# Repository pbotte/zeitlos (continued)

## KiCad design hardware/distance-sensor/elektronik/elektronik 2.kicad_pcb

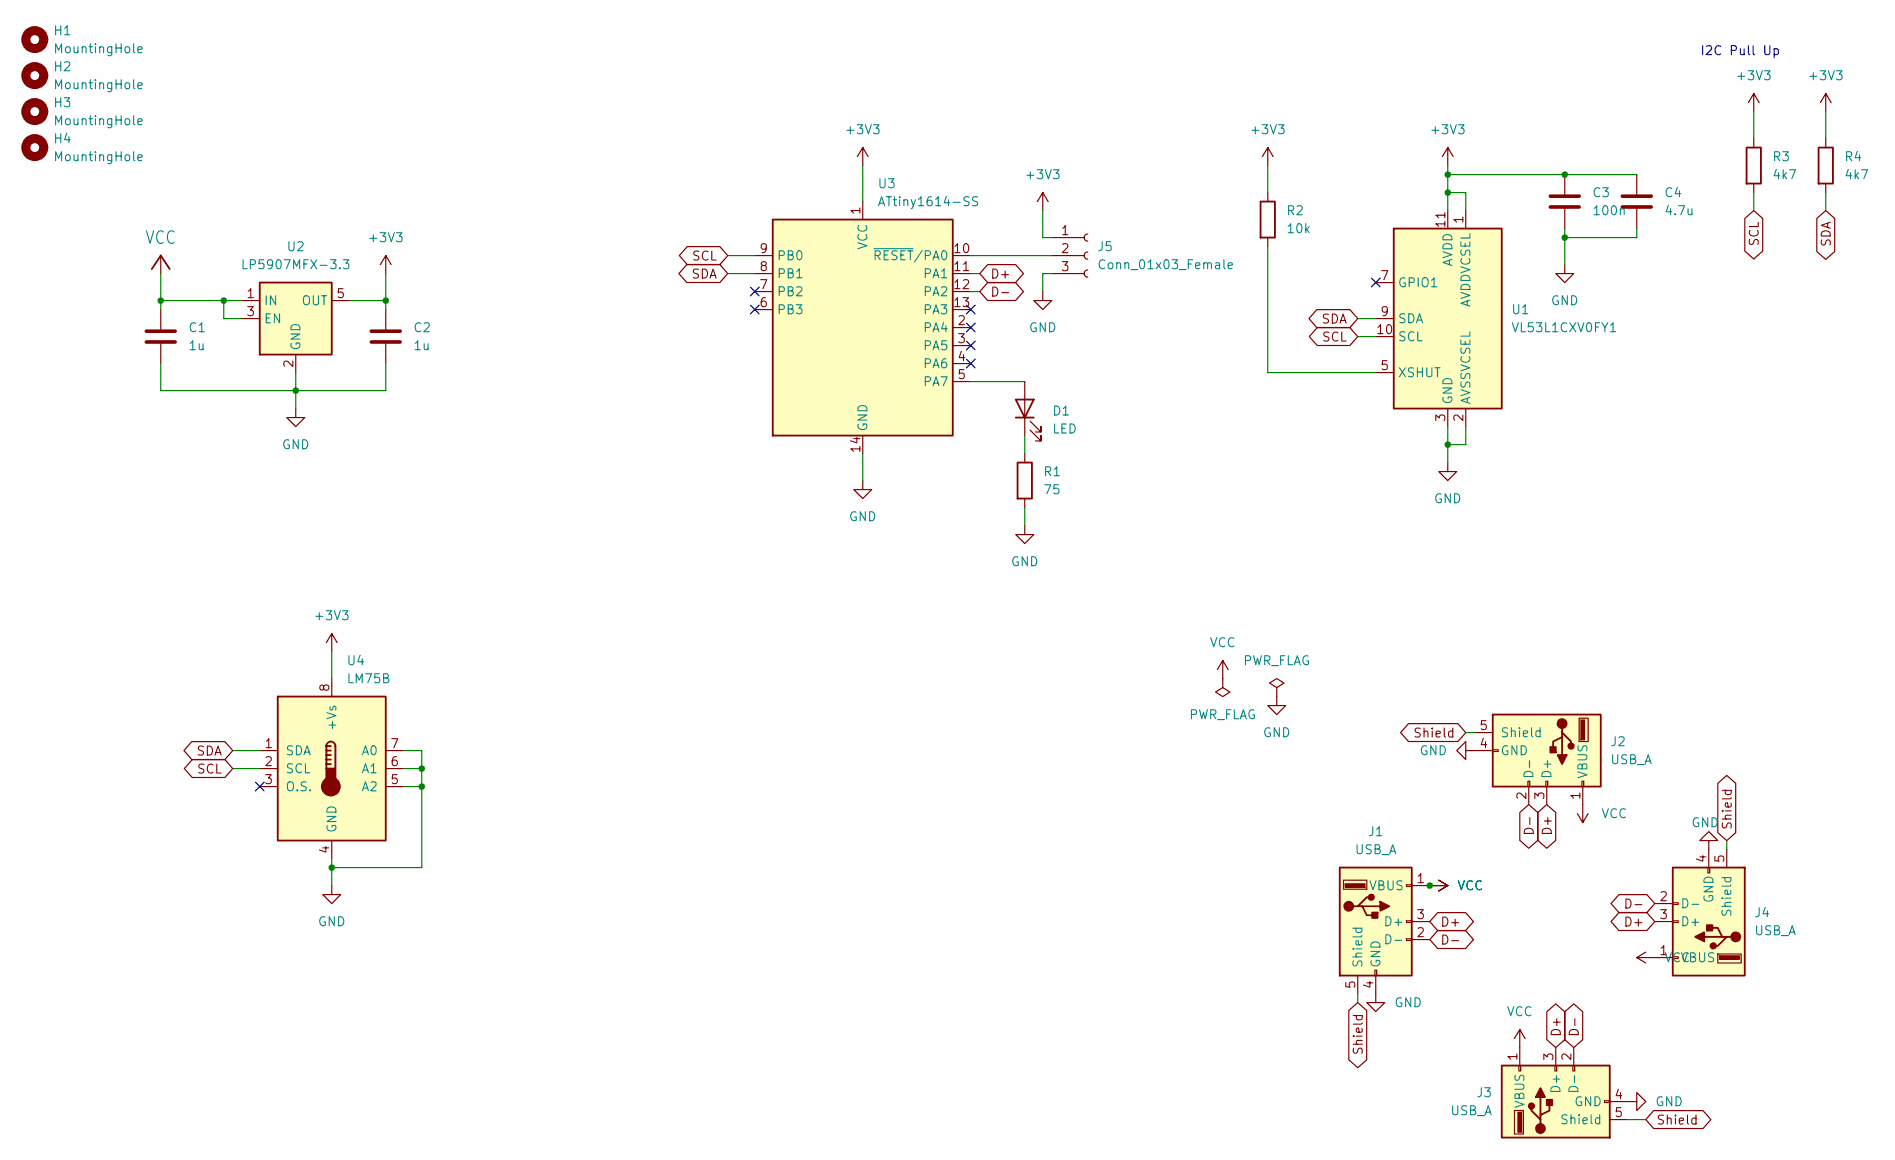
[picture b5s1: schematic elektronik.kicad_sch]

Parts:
C1, C2: 1u; C_1206_3216Metric
C3: 100n; R_1206_3216Metric
C4: 4.7u; R_1206_3216Metric
D1: LED; LED_1206_3216Metric
H1, H2, H3, H4: MountingHole; MountingHole_3.2mm_M3
J1, J2, J3, J4: USB_A; Conn_USB_A_Jack
J5: Conn_01x03_Female; PinSocket_1x03_P2.54mm_Vertical
R1: 75; R_1206_3216Metric
R2: 10k; R_1206_3216Metric
R3, R4: 4k7; R_1206_3216Metric
U1: VL53L1CXV0FY1; ST_VL53L1x
U2: LP5907MFX-3.3; SOT-23-5
U3: ATtiny1614-SS; SOIC-14_3.9x8.7mm_P1.27mm
U4: LM75B; VSSOP-8_3.0x3.0mm_P0.65mm

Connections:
+3V3: C2.1, C3.1, C4.1, J5.1, R2.1, R3.1, R4.1, U1.1 (AVDDVCSEL), U1.11 (AVDD), U2.5 (OUT), U3.1 (VCC), U4.8 (+Vs)
D+: J1.3 (D+), J2.3 (D+), J3.3 (D+), J4.3 (D+), U3.11 (PA1)
D-: J1.2 (D-), J2.2 (D-), J3.2 (D-), J4.2 (D-), U3.12 (PA2)
GND: C1.2, C2.2, C3.2, C4.2, J1.4 (GND), J2.4 (GND), J3.4 (GND), J4.4 (GND), J5.3, R1.2, U1.2 (AVSSVCSEL), U1.3 (GND), U1.4 (GND), U1.6 (GND), U1.12 (GND), U2.2 (GND), U3.14 (GND), U4.4 (GND), U4.5 (A2), U4.6 (A1), U4.7 (A0)
unnamed: D1.1 (K), R1.1
unnamed: D1.2 (A), U3.5 (PA7)
unnamed: J5.2, U3.10 (~RESET/PA0)
unnamed: R2.2, U1.5 (XSHUT)
SCL: R3.2, U1.10 (SCL), U3.9 (PB0), U4.2 (SCL)
SDA: R4.2, U1.9 (SDA), U3.8 (PB1), U4.1 (SDA)
Shield: J1.5 (Shield), J2.5 (Shield), J3.5 (Shield), J4.5 (Shield)
VCC: C1.1, J1.1 (VBUS), J2.1 (VBUS), J3.1 (VBUS), J4.1 (VBUS), U2.1 (IN), U2.3 (EN)

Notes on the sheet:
I2C Pull Up

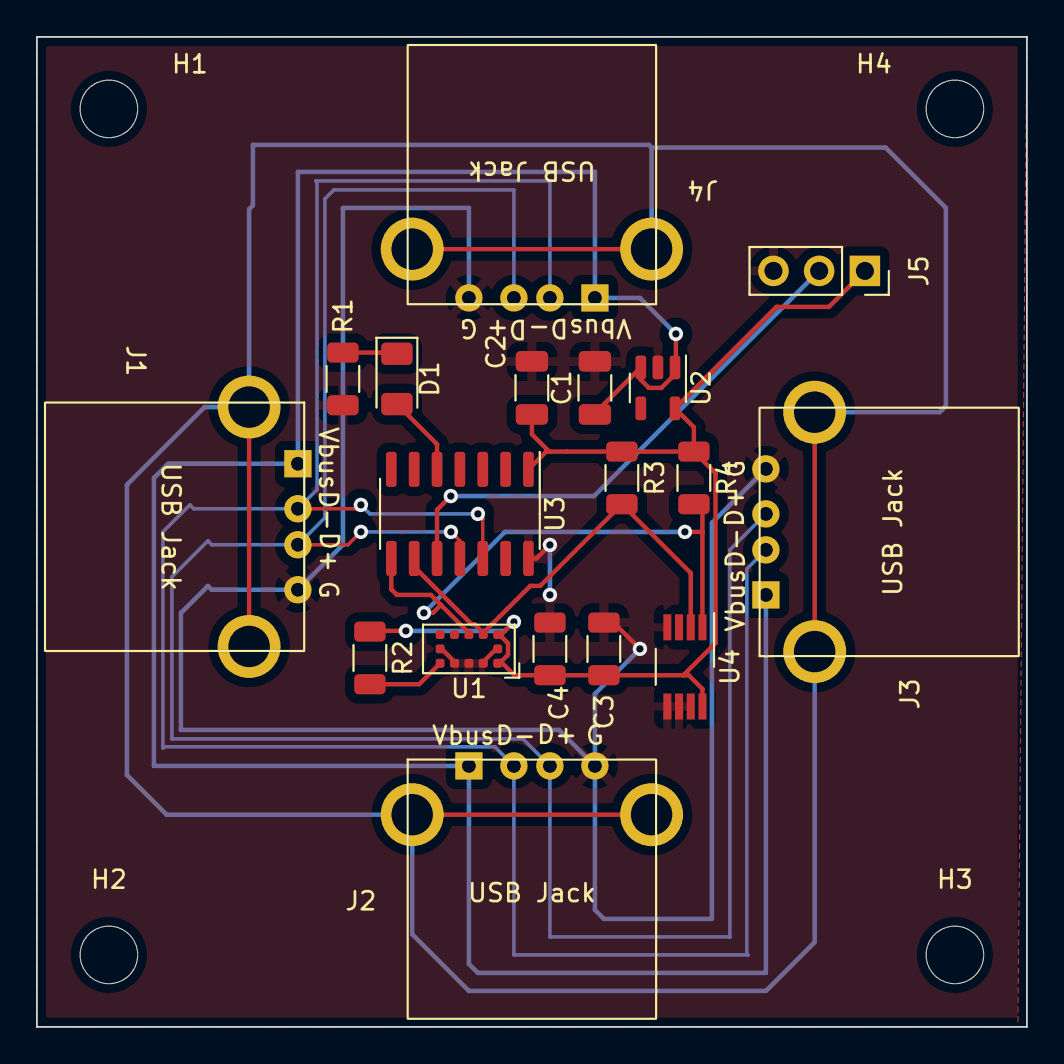
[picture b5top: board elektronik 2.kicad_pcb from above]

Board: 2 copper layers, 55.0 x 55.0 mm, 22 parts (0 on the bottom side), 12 nets.

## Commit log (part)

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2019-08-31 Working updates with AtMega on eink display
2019-09-07 added full refresh at start
2019-09-07 qr code added
2019-10-18 Design der Anzeige verbessern.
2019-10-18 Erste Schritte zur Seriellen Komminukation zum PC
2019-10-19 Towards 2way communication between computer and controller
2019-10-20 sending refresh via MQTT works.
2019-10-23 SN Readout corrected
2019-10-24 udev rule for automated lauch added.
2019-10-25 automatic start and stop of scale controller.py
2019-11-09 Anzeige von Produkt-Typ und Beschreibung + MQTT Name
2019-11-17 Added Q4HX711 lib
2019-11-17 clean up
2019-12-05 display rotated to give space for RFID
2019-12-06 Parallel readout of all hx711 working, display disabled.
2019-12-06 working intermediate state
2019-12-07 pn532 readout added
2019-12-07 Added NFC code
2019-12-08 add client live display
2019-12-08 intermediate step
2019-12-09 intermediate
2019-12-11 Einfache Waage hinzugefügt.
2019-12-12 Images added
2019-12-13 Verwaltung hinzugefügt
2020-01-26 Neueste Waagen hinzugefügt
2020-01-26 Create LICENSE
2020-02-07 Readme updated
2020-05-10 Details zum Aufbau
2020-05-10 Aufbau
2020-05-10 Aufbaubeschreibung (kleine Änderung)
2020-05-11 Letzte Änderungen von Dez 2019 aufnehmen
2020-10-28 Door control working
2020-10-28 Submodules in www added
2020-10-29 working prototype
2020-11-02 Breite der Fräsung für Trenner: 2.0mm
    Kleine Änderung bei der Breite der Einfräsung für Trenner: Jetzt 2.0mm anstatt zuvor 2.1mm. Durch das Werkzeug allein wird später der 2.0mm breite Trenner gut passen.
2021-01-17 Beispielansicht-Einkauf
2021-01-17 Beispieleinkaufbilder
2021-01-17 Beispielbilder
2022-02-19 reorganisation
2022-02-19 moved files: links corrected
2022-02-19 pictures aded
2022-02-20 fues added and small movements
2022-02-25 interactive HTML-BOM added
2022-03-06 second LDO for eink added
2022-03-07 JP1 added
2022-03-13 Error on JP1 fixed and changed scale wires pads
2022-03-23 bus terminator and shelf controller added
2022-03-27 Autoamtic versioning on every compile added
2022-03-27 ADC averaging with ring buffer added
2022-05-31 Bilder hinzugefügt
2022-07-10 40pol connector rotated and other small mods.
2022-07-11 Shelf controller initial commit
2022-07-12 long variable functionality added
2022-07-17 more CAN commands added
2022-07-27 Clean up of old unused stuff from USB era
2022-07-27 rename of shop-control
2022-07-27 door display updated
2022-08-02 First running version of qr-scanner
2022-08-04 qr code scanner fully ready
2022-08-06 firmware widthdrawn units hinzugefügt
2022-09-15 price per unit added
2022-09-15 shop-control and www improvements
2022-09-15 shop controller service added
2022-09-17 Small changes in shop control
2022-09-18 Warenkorb besser lesbar
2022-10-08 tracker and io-input-2-serial added
2022-10-15 io-input-2-serial modified
2022-10-23 Update ablauf.md
    Änderungen mit Distanzsensoren und OHNE Bestätigungsmodul im Laden.
2022-10-24 Update ablauf.md
    Unter Berücksichtigung, dass die Distanzsensoren nicht immer alle Personen im Raum abdecken. Außerdem kann die Tür die Sensoren negativ beeinflussen.
2022-10-24 Logik anpassungen und mehr
2022-10-25 save_last_debug_picture feature added
2022-10-25 new FSM logic and last qr-scanner-debug picture added
2022-10-29 small mods and error corrections
2022-10-30 small error corrections for shop-control and more small fixes
2022-10-31 mqtt-2-ntfy added
2022-10-31 Update ablauf.md
    - [ ] Neuer Zustand vor dem Öffnen des Ladens: Vorbereiten der Wagen, dann erst betreten
    - [ ] Neuer Zustand einfügen vor 5: Warenkorb wird übermittelt für die Rechnung
2022-10-31 First version display-power-control added
2022-10-31 improvements to display-power-control
2022-10-31 Display power switches added to nodered
2022-11-01 new states added to shop-controller
2022-11-03 minor fix for shop-controller and lights added to nodered
2022-11-05 shop master with imporved DB connectivity and signal handler for graceful exit
2022-11-05 more averaging to compensate daylight
2022-11-07 invoices display aded
2022-11-09 PHP code snippets from public webpage saved
2022-11-14 Watchdog added
2022-11-14 small changes to shop-control and door display
2022-11-19 changed to sequential mqtt handling
2022-11-19 updater for webpage added
2022-11-20 service file imporved
2022-11-20 added payment via paypal
2022-11-20 small changes to Nodered and paypal image added
2022-11-24 shop-control switches light via Generic_PIR
2022-11-24 upload.sh now switches light
2023-01-12 added tcr_async.py script for zvt terminal
2023-01-23 split .gitignore to subfolders
2023-01-23 preauth working
2023-01-29 Waage mit Schalter UND Distance-Sensor hinzugefügt
2023-01-29 cleanup part 2
2023-01-29 moved older version to corresponding directories
2023-03-15 actual status Waage V4 added
2023-03-17 tcr control updated
2023-04-14 card_reader zwischenstand mit mehr Funktionen
2023-04-16 card reader updates
2023-04-16 activate service menu cmd added
2023-04-16 added method for running with timeout
2023-04-16 send terminal text output to mqtt server
2023-04-16 small bug fixes
2023-04-25 small updates to PCB design
2023-04-25 use latin-1 as encoding
2023-04-25 detect text block and send by mqtt
2023-05-01 removed unneceasary lines
2023-05-01 Ablaufplan gerändert auf Kartenterminal
2023-05-07 Rechnungen als PDF via Webserver
2023-05-07 Zum öffentlichen WWW-Server verschoben
2023-05-07 readme improved
2023-05-08 changes to make comments send from PT always work
2023-05-20 Terminal Timeout state reordered
2023-05-20 Ablauf angepasst
2023-05-20 towards cardreader integration
2023-05-26 towards card reader solution
2023-05-29 towards invoice on outside display
2023-05-29 bug fix, falls crc32 mit 0 beginnt.
2023-06-14 added basic construct for lidar
2023-06-24 submodules for software/www/ added
2023-06-24 lidar readout
2023-07-17 firmware v4 added
2023-07-25 I2C Zwischenstand
2023-07-26 intermediate i2c updates
2023-07-27 towards working firmware (most of it working)
2023-07-29 erster Suchlauf komplett erfolgreich
2023-08-11 bug fix
2023-08-11 change MAC adresse to inherit from serial number
2023-11-07 scale_v4 updates
2023-11-07 Datein für die Produktion
2023-11-07 Shelf Controller Auslese Update
2023-11-11 added qrcode lib for old scale firmware
2023-11-11 waveshare readout added
2023-11-11 cleanup of old data
2023-12-14 super small mod
2023-12-24 shop-track-collector added
2023-12-24 more parameters
2023-12-25 Weitere Funktionen für Firmware
2023-12-25 Weitere Verbesserungen Regalauslese
2023-12-26 Uploading Version 65240
2023-12-29 Renaming CAN stuff
2023-12-29 Doku ergänzt
2023-12-30 Make shop-track-collector work
2023-12-30 clean up old stuff
2024-01-01 Prepare for >8 scales per controller
2024-01-02 IP address adpated
2024-01-02 improved result parsing
2024-01-09 Kostenübersicht hinzugefügt.
2024-01-14 Autostart for scales added
2024-01-14 udev rules for tof tracker added.
2024-01-14 bug corrected
2024-01-14 bug fix 2
2024-01-16 Startseite angepasst
2024-01-16 Aufräumen
2024-01-25 Ansichten hinzufügen
2024-01-26 raspi images get.sh script
2024-01-27 get.sh improved
2024-01-27 install script updated
2024-01-27 file now executeable
2024-01-27 install script added
2024-01-28 get.sh updated
2024-01-28 small update to get.sh
2024-01-28 small update
2024-01-28 add install script
2024-01-28 added start and enable
2024-03-17 PoE+ HAT added
2024-03-27 Updates to install script and archive VL53L1 readout
2024-03-28 partial upgrade for paho version 2
2024-03-29 service file and requirements updated
2024-03-29 cardreader age test
2024-03-29 reduce sensitivity for TOF changes
2024-03-29 small changes for Nodered and shop-control
2024-03-29 correct TOF 4x4 heatmap
2024-03-30 service file for display power control without debug
2024-04-02 shelf-controller mqtt name changed
2024-04-02 shop-track mqtt name extended
2024-04-03 shop-control updates
2024-04-03 Wegfall einer Altlast.
2024-04-04 Neue Browser Kiosk Methode
2024-04-04 Introducing VAT to products
2024-04-04 Update company name
2024-04-04 added more shop-displays
2024-04-04 some bug fixes
2024-04-04 another small bug fix
2024-04-04 x-file bit added
2024-04-05 implemented sending state topic 0/1 if running
2024-04-07 bug fix for calculation of average
2024-04-07 bug fix for min std-deviation
2024-04-07 Nodered: Waagen-Produkt-Zuordnung angefangen Bug-fixes für shop-controller
2024-04-08 small add ons for debug and sorting of goods
2024-04-11 Anpassung der Readme
2024-04-11 Doku erweitert
2024-04-11 Öffnung des Ladens für Testkäufer via Remote MQTT-Broker, Bug fix für Summenberechnung falls Produkt auf mehreren Waagen, Artikelpflege via Nodered
2024-04-11 Kassenbon-Anzeige korrigiert
2024-04-14 Autoreconnect zum MQTT Server sollte nun funktionieren bei Verbindungsabbruch
2024-04-14 Einzelne Waagen können via set_zero cmd hinzugefügt werden In Nodered SQL angepasst für Lieferant -> Supplier
2024-04-14 Remote Steuerung für den Laden via MQTT
2024-04-19 Sync der DB und Zugriff für Lieferanten
2024-04-19 Rechnungen anzeigen und Sync zur remote DB
2024-04-19 Produktezuordnung Waagen setzen
2024-04-20 Massenänderungen bei Waagen-Produkt-Zuordnung vornehmen können über Webseite
2024-04-20 Waagenkalibration wieder ermöglicht
2024-04-21 Added functionality to submit all mass values within 5 seconds after last touch
2024-04-27 shop-tts added
2024-04-27 TTS unterstützen und kleine Verbesserungen
2024-04-28 Änderungen durch öffentliche Webseite möglich im Shop-Controller
2024-05-06 bug fix und tipps aufgenommen
2024-05-18 Fix for cardreader (Nachbuchungen are now handled correctly)
2024-05-18 Spracheausgabe: X auf Boden suchen Testkunden: Licht aus am Ende Pfandrückgabe: Negative Produktmasse erlauben
2024-05-18 PCB drawings added
2024-05-20 MQTT für tof_cam hinzugefügt
2024-05-20 small improvement for cardread but no real fix
2024-05-20 tof-camera added service and install.sj
2024-05-20 tof-camera set_zero on shop-status
2024-05-21 multiple scales per product but one common mass in calculation
2024-05-21 Warenkorb Korrekturen via Webpage
2024-05-21 Warenkorb aus der Ferne bearbeiten, HTML Seite
2024-05-22 VAT bug fixed local display
2024-05-22 VAT bugfix public www
2024-05-22 small mods
2024-05-24 firmware and converter for eink display
2024-06-12 eink webserver - first draft
2024-06-13 webserver verbesserung
2024-06-15 termination improved
2024-06-15 added correct termination via service added state=0/1
2024-06-15 added state tio io-usb-control
2024-06-15 added state to shop-track
2024-06-15 state for track-collector and msg rate limit
2024-06-15 make eink webserver.py executable
2024-06-15 added script for easy update of clients
2024-06-15 improvements for update_all_pis script
2024-06-15 state for tts added
2024-06-15 state for tof camera
2024-06-15 added state to eink web server
2024-06-15 added check for sub systems added state to eink web server
2024-06-15 bugfix
2024-06-15 Sub system check also in state 7 (before only in 1)
2024-06-19 Unterstützung für Doppelbreite Waagen bei Zuweisung
2024-06-19 HTTP Server für QR-Code als PNG-Anzeige
2024-06-20 scales_products and more now via MQTT submitted
2024-06-20 httpserver for future development
2024-06-22 improvements to eink webserver
2024-06-22 eink pico firmware first attempt
2024-06-22 gitignore adjusted
2024-06-23 working eink firmware
2024-06-23 improvement for myconfig.py
2024-06-28 Bugfixes und Anpassungen:
    timeouts angepasst, damit bei längerer Nutzung des Kartenterminals es zu keinem technischen Fehler des Ladens kommt. Außerdem soll man die Türe auch bei Zustand 8 öffnen können.
    Wenn es zu einem Lesefehler bei einer Waage kommt, soll nicht gleich das ganze Skript abstürzen.
    sync_to_mysql.py jetzt mit sync-bit
    Filter bei mqtt-2-ntfy auf interessante Dinge um nicht ins Limit zu laufen.
2024-06-30 webpage adjusted for set_shop_status
2024-06-30 - Durchsage bei Maximalbetrag - Timeout für Kunde im Laden nun nach Zustand 4 - Vorauthorisierungsbetrag ist nun in Variable
2024-06-30 Zustand 20 hinzugefügt, Warenkorb zu voll.
